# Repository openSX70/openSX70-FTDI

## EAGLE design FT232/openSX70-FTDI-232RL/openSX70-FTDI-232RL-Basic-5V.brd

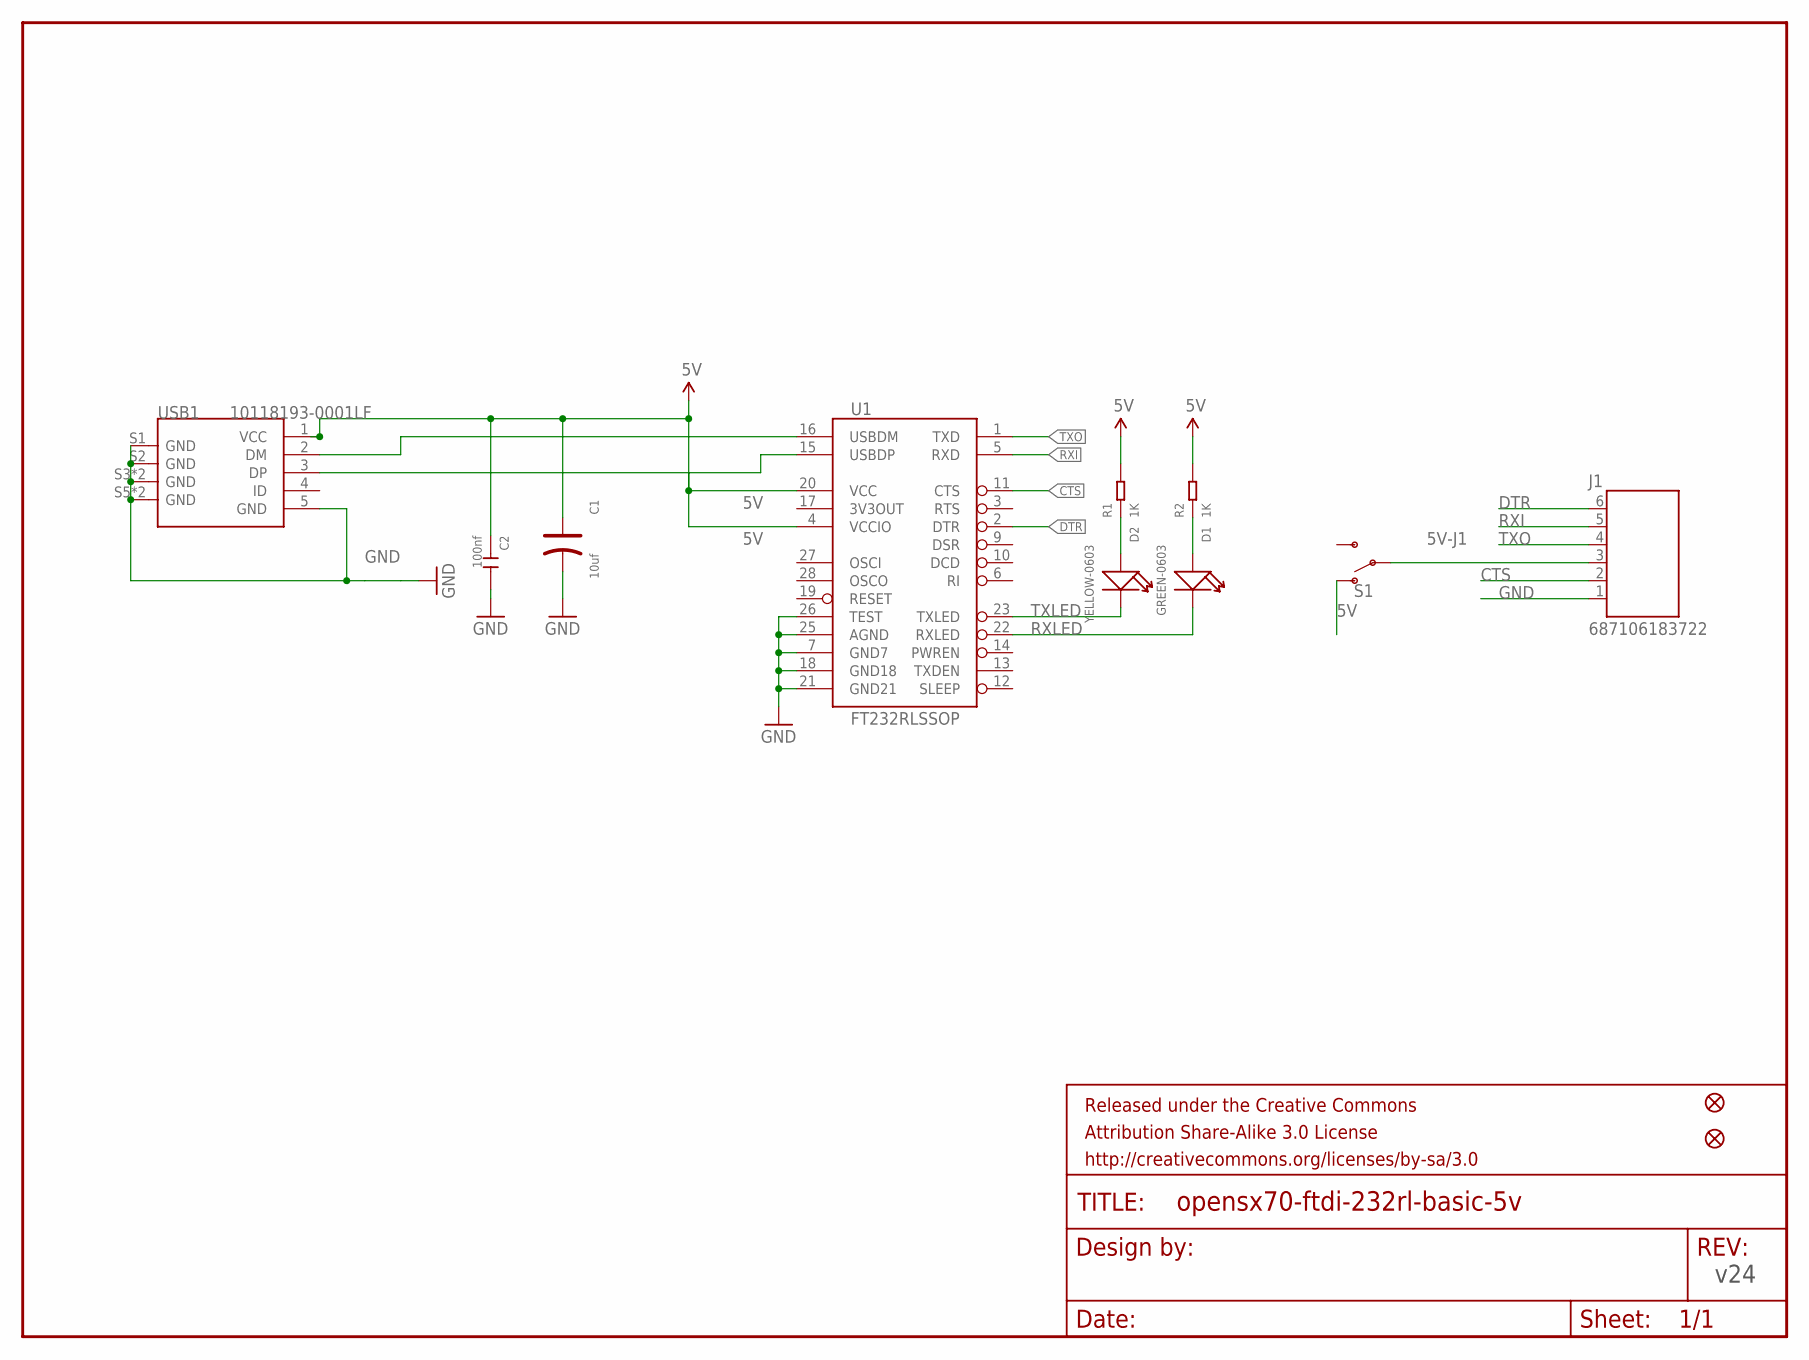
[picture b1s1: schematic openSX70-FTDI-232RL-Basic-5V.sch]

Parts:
C1: 10uf; AVX-A
C2: 100nf; C0603
D1: GREEN-0603; LED-0603
D2: YELLOW-0603; LED-0603
FRAME1: FRAME-LETTER; CREATIVE_COMMONS
J1: 687106183722
JP3, JP5: FIDUCIAL1X2; FIDUCIAL-1X2
R1, R2: 1K; R0603
S1: SWITCH-SPDT-SMD-RIGHT-ANGLE; SWITCH_SPST_SMD_A
U1: FT232RLSSOP; SSOP28DB
USB1: 10118193-0001LF; MICRO-USB5+6P-SMD-0.65-B

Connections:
5V: C1.+, C2.1, R1.2, R2.2, S1.1 (O), U1.4 (VCCIO), U1.20 (VCC), USB1.1 (VCC)
5V-J1: J1.3 (4), S1.2
CTS: J1.2 (5), U1.11 (CTS)
DTR: J1.6 (1), U1.2 (DTR)
GND: C1.-, C2.2, J1.1 (6), U1.7 (GND7), U1.18 (GND18), U1.21 (GND21), U1.25 (AGND), U1.26 (TEST), USB1.5 (GND), USB1.S1 (GND), USB1.S2 (GND), USB1.S3 (GND), USB1.S4 (GND), USB1.S5 (GND), USB1.S6 (GND)
unnamed: D2.+, R1.1
unnamed: D1.+, R2.1
unnamed: U1.16 (USBDM), USB1.2 (DM)
RXI: J1.5 (2), U1.5 (RXD)
RXLED: D1.-, U1.22 (RXLED)
TXLED: D2.-, U1.23 (TXLED)
TXO: J1.4 (3), U1.1 (TXD)
USB_D+: U1.15 (USBDP), USB1.3 (DP)

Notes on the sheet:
v24

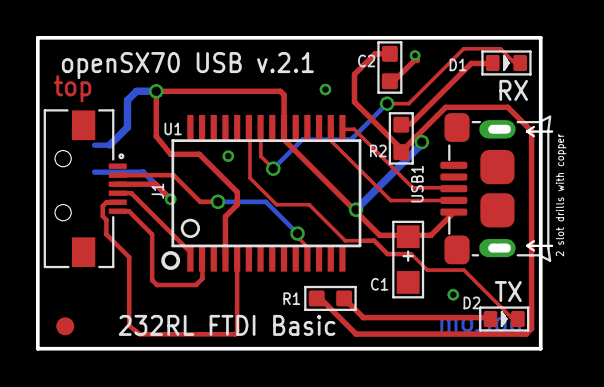
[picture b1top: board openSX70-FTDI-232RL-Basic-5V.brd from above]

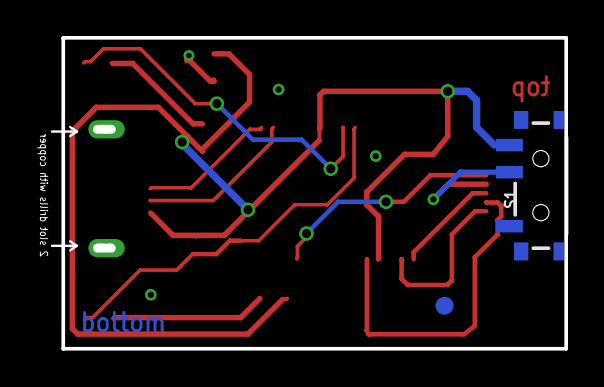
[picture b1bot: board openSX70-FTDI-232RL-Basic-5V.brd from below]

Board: 2 copper layers, 28.6 x 17.3 mm, 13 parts (2 on the bottom side), 13 nets.

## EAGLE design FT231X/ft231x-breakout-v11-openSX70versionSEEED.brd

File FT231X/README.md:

# openSX70-FTDI
FTDI connection to program openSX70 camera

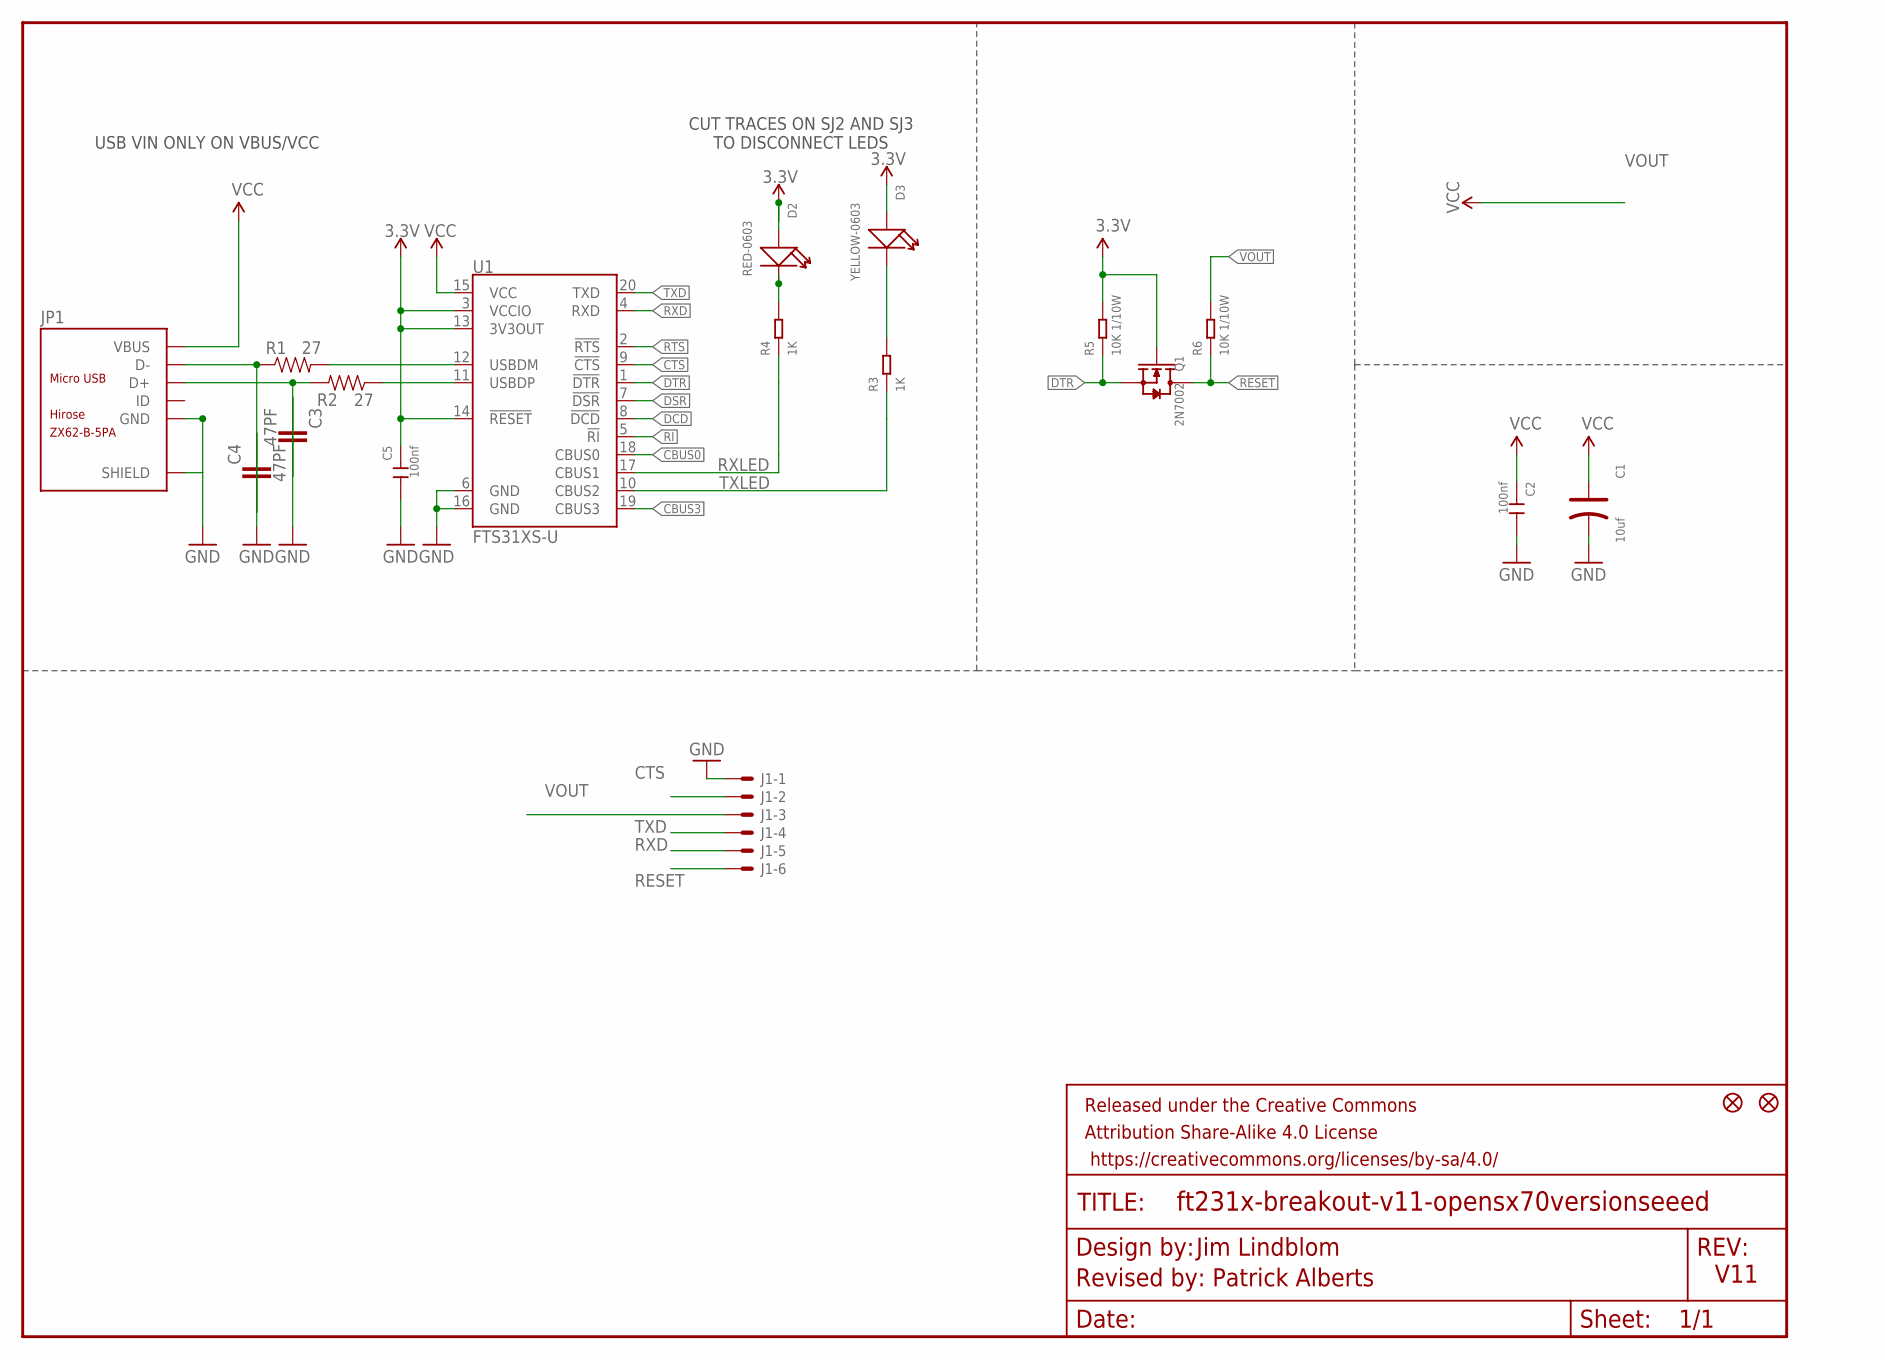
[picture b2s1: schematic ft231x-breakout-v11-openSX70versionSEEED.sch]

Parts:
C1: 10uf; AVX-B
C2, C5: 100nf; C0603
C3, C4: 47PF; CC0603KRX7R9BB473_CAPC1608X90
D2: RED-0603; LED-0603
D3: YELLOW-0603; LED-0603
FRAME1: FRAME-LETTER; CREATIVE_COMMONS
J1: XF2L-0625-1
JP1: ZX62-B-5PA; MICRO-USB5+6P-SMD-0.65-AB
JP5, JP6: FIDUCIAL1X2; FIDUCIAL-1X2
Q1: 2N7002; SOT-23
R1, R2: 27; 0603-RES
R3, R4: 1K; R0603
R5, R6: 10K 1/10W; R0603
U1: FTS31XS-U; SSOP20_L

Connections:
3.3V: C5.1, D2.+, D3.+, Q1.1 (G), R5.2, U1.3 (VCCIO), U1.13 (3V3OUT), U1.14 (!RESET)
CBUS0: U1.18 (CBUS0)
CBUS3: U1.19 (CBUS3)
CTS: J1.2, U1.9 (!CTS)
DCD: U1.8 (!DCD)
DSR: U1.7 (!DSR)
DTR: Q1.2 (S), R5.1, U1.1 (!DTR)
GND: C1.-, C2.2, C3.2, C4.2, C5.2, J1.1, JP1.5 (GND), JP1.P1 (SHIELD), JP1.P2 (SHIELD), JP1.P3_1 (SHIELD), JP1.P3_2 (SHIELD), JP1.P3_3 (SHIELD), JP1.P4_1 (SHIELD), JP1.P4_2 (SHIELD), JP1.P4_3 (SHIELD), JP1.P5 (SHIELD), JP1.P6 (SHIELD), U1.6 (GND), U1.16 (GND)
unnamed: R1.2, U1.12 (USBDM)
unnamed: R2.1, U1.11 (USBDP)
unnamed: C3.1, JP1.3 (D+), R2.2
unnamed: C4.1, JP1.2 (D-), R1.1
unnamed: D3.-, R3.2
unnamed: D2.-, R4.2
RESET: J1.6, Q1.3 (D), R6.1
RI: U1.5 (!RI)
RTS: U1.2 (!RTS)
RXD: J1.5, U1.4 (RXD)
RXLED: R4.1, U1.17 (CBUS1)
TXD: J1.4, U1.20 (TXD)
TXLED: R3.1, U1.10 (CBUS2)
VCC: C1.+, C2.1, JP1.1 (VBUS), U1.15 (VCC)
VOUT: J1.3, R6.2

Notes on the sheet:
V11
Jim Lindblom
Revised by: Patrick Alberts
USB VIN ONLY ON VBUS/VCC
CUT TRACES ON SJ2 AND SJ3 TO DISCONNECT LEDS

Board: 2 copper layers, 20 parts (0 on the bottom side), 17 nets, no tracks yet.

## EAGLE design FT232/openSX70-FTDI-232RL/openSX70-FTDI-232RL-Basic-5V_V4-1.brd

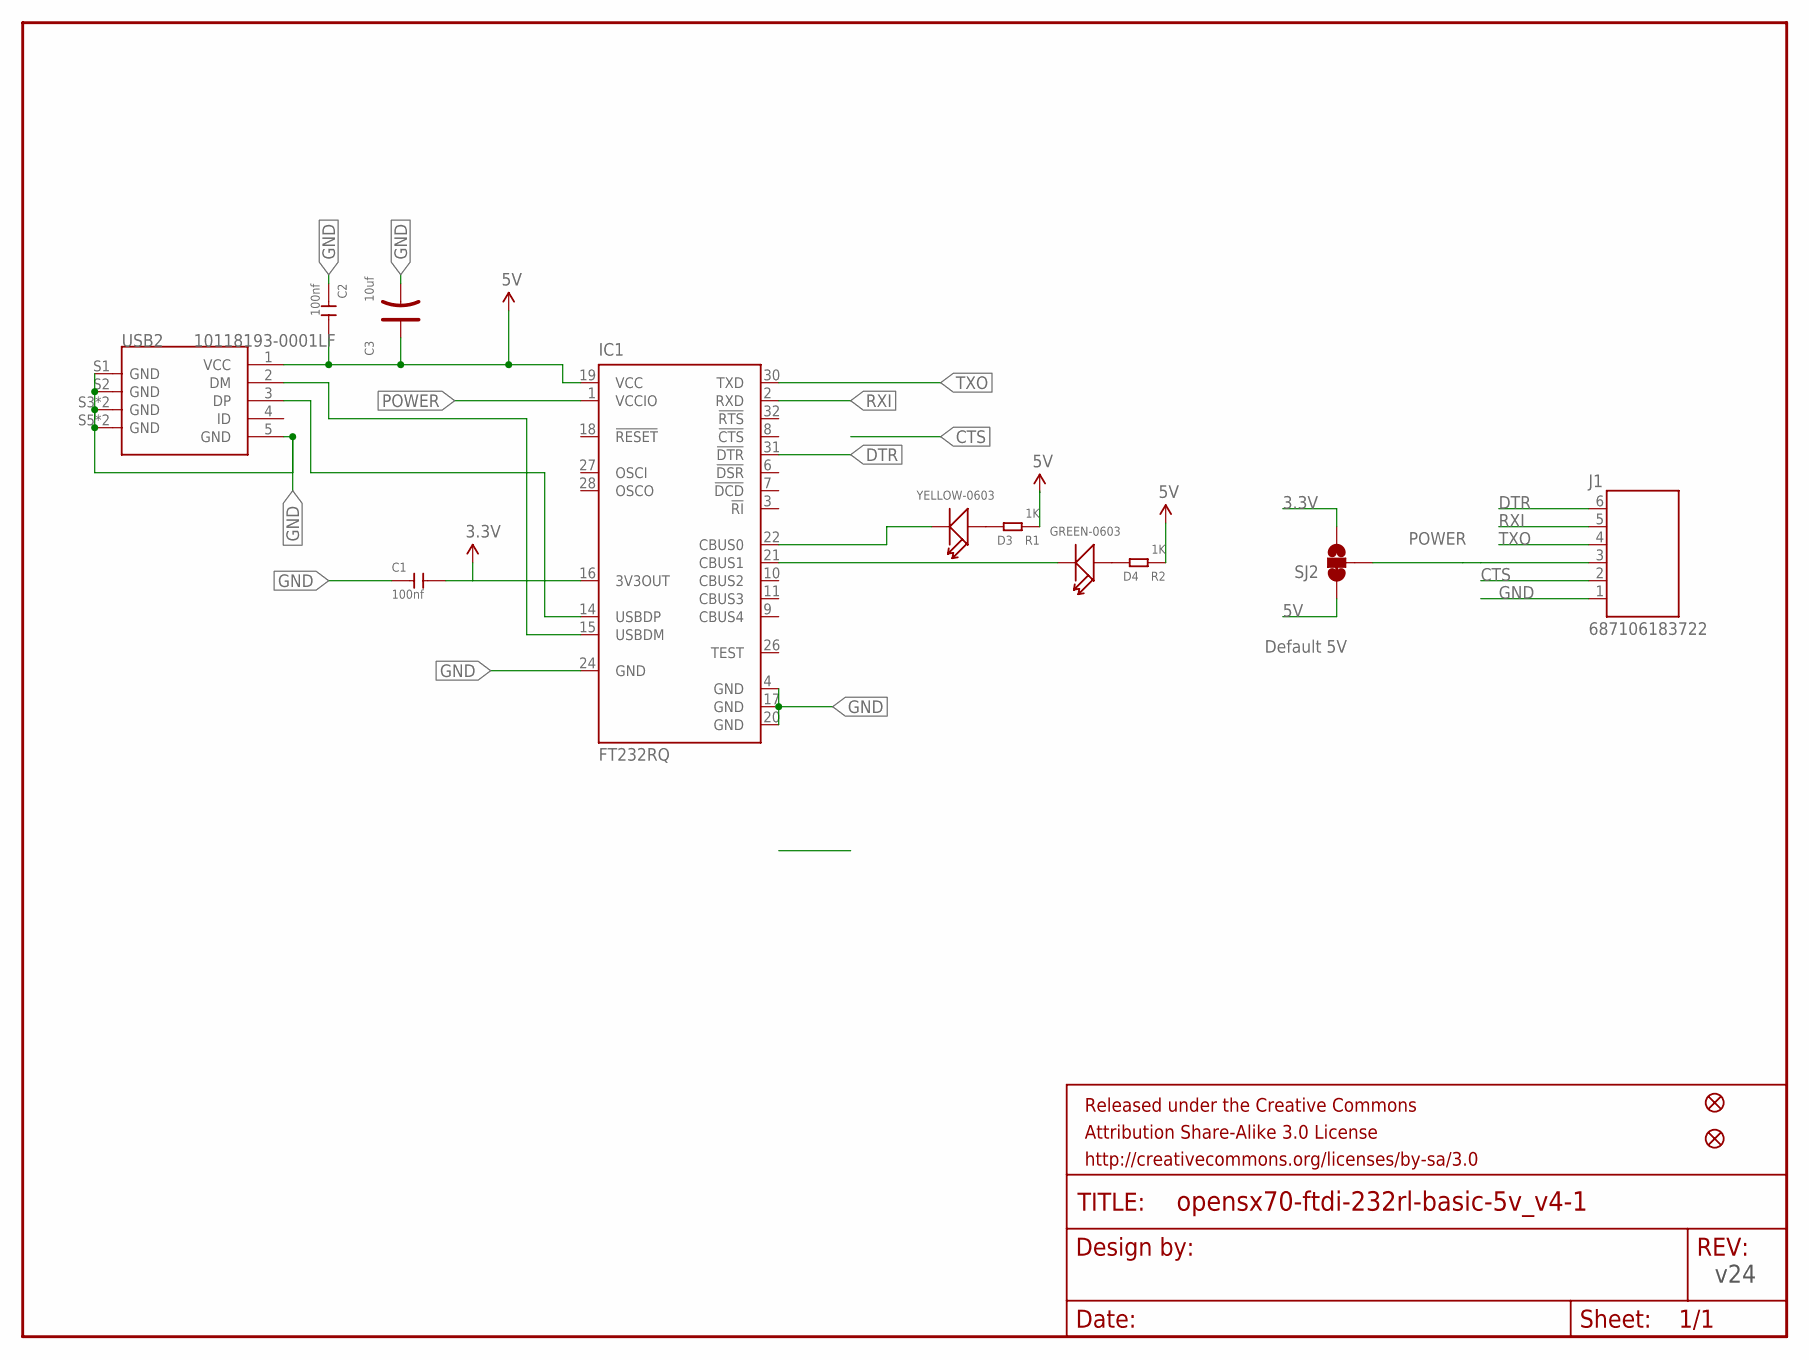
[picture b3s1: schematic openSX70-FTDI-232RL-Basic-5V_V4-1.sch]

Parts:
C1, C2: 100nf; C0603
C3: 10uf; AVX-A
D3: YELLOW-0603; LED-0603
D4: GREEN-0603; LED-0603
FRAME1: FRAME-LETTER; CREATIVE_COMMONS
IC1: FT232RQ; QFN32
J1: 687106183722
JP3, JP5: FIDUCIAL1X2; FIDUCIAL-1X2
R1, R2: 1K; R0603
SJ2: SOLDERJUMPER_2WAYS; SJ_3
USB2: 10118193-0001LF; MICRO-USB5+6P-SMD-0.65-B

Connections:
3.3V: SJ2.3
5V: C2.2, C3.+, IC1.19 (VCC), R1.1, R2.1, SJ2.1, USB2.1 (VCC)
CTS: IC1.8 (!CTS), J1.2 (5)
DTR: IC1.31 (!DTR), J1.6 (1)
GND: C1.1, C2.1, C3.-, IC1.4 (GND), IC1.17 (GND), IC1.20 (GND), IC1.24 (GND), J1.1 (6), USB2.5 (GND), USB2.S1 (GND), USB2.S2 (GND), USB2.S3 (GND), USB2.S4 (GND), USB2.S5 (GND), USB2.S6 (GND)
unnamed: IC1.15 (USBDM), USB2.2 (DM)
unnamed: IC1.14 (USBDP), USB2.3 (DP)
unnamed: D3.-, IC1.22 (CBUS0)
unnamed: D4.-, IC1.21 (CBUS1)
unnamed: D3.+, R1.2
unnamed: D4.+, R2.2
POWER: IC1.1 (VCCIO), J1.3 (4), SJ2.2
RXI: IC1.2 (RXD), J1.5 (2)
TXO: IC1.30 (TXD), J1.4 (3)
VCC: C1.2, IC1.16 (3V3OUT)

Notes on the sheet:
Default 5V
v24

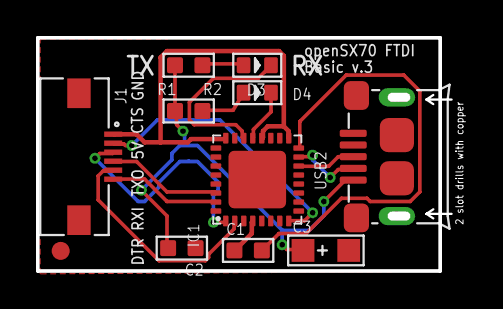
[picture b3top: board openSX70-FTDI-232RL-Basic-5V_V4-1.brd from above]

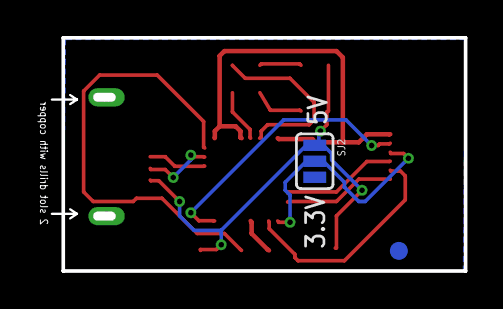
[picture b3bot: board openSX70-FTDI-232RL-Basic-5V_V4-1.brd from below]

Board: 2 copper layers, 23.0 x 13.0 mm, 14 parts (2 on the bottom side), 14 nets.

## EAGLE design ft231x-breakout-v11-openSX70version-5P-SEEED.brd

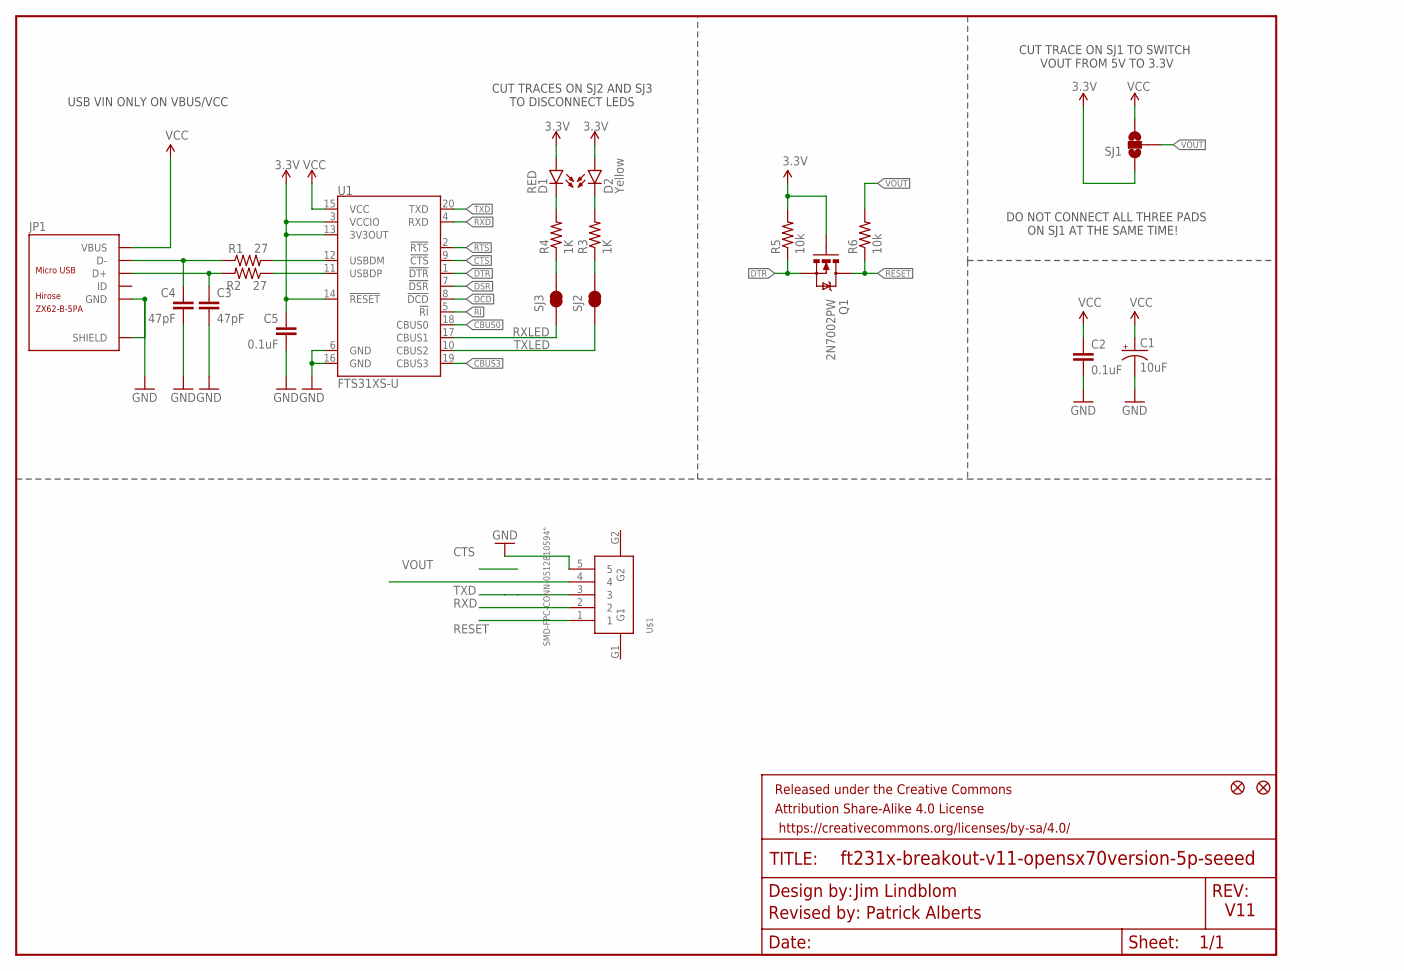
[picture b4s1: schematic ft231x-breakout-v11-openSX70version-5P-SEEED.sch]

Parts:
C1: 10uF; EIA3216
C2, C5: 0.1uF; 0603-CAP
C3, C4: 47pF; 0603-CAP
D1: RED; LED-0603
D2: Yellow; LED-0603
FRAME1: FRAME-LETTER; CREATIVE_COMMONS
JP1: ZX62-B-5PA; MICRO-USB5+6P-SMD-0.65-AB
JP5, JP6: FIDUCIAL1X2; FIDUCIAL-1X2
Q1: 2N7002PW; SOT323
R1, R2: 27; 0603-RES
R3, R4: 1K; 0603-RES
R5, R6: 10k; 0603-RES@1
SJ1: SOLDERJUMPER_2WAYS; SJ_3
SJ2: TXLED; SJ_2S-TRACE
SJ3: RXLED; PAD-JUMPER-2-NC_BY_TRACE_YES_SILK
U1: FTS31XS-U; SSOP20_L
U$1: SMD-FPC-CONN-0512810594"; 51281-0594

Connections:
3.3V: C5.1, D1.A, D2.A, Q1.1 (G), R5.2, SJ1.1, U1.3 (VCCIO), U1.13 (3V3OUT), U1.14 (!RESET)
CBUS0: U1.18 (CBUS0)
CBUS3: U1.19 (CBUS3)
CTS: U1.9 (!CTS)
DCD: U1.8 (!DCD)
DSR: U1.7 (!DSR)
DTR: Q1.2 (S), R5.1, U1.1 (!DTR)
GND: C1.C (-), C2.2, C3.2, C4.2, C5.2, JP1.5 (GND), JP1.P1 (SHIELD), JP1.P2 (SHIELD), JP1.P3 (SHIELD), JP1.P4 (SHIELD), JP1.P5 (SHIELD), JP1.P6 (SHIELD), U1.6 (GND), U1.16 (GND), U$1.5
unnamed: R1.2, U1.12 (USBDM)
unnamed: R2.1, U1.11 (USBDP)
unnamed: C3.1, JP1.3 (D+), R2.2
unnamed: C4.1, JP1.2 (D-), R1.1
unnamed: D2.C, R3.2
unnamed: D1.C, R4.2
unnamed: R3.1, SJ2.2
unnamed: R4.1, SJ3.2
RESET: Q1.3 (D), R6.1, U$1.1
RI: U1.5 (!RI)
RTS: U1.2 (!RTS)
RXD: U1.4 (RXD), U$1.2
RXLED: SJ3.1, U1.17 (CBUS1)
TXD: U1.20 (TXD), U$1.3
TXLED: SJ2.1, U1.10 (CBUS2)
VCC: C1.A (+), C2.1, JP1.1 (VBUS), SJ1.3, U1.15 (VCC)
VOUT: R6.2, SJ1.2, U$1.4

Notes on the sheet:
V11
Jim Lindblom
Revised by: Patrick Alberts
USB VIN ONLY ON VBUS/VCC
CUT TRACES ON SJ2 AND SJ3 TO DISCONNECT LEDS
CUT TRACE ON SJ1 TO SWITCH VOUT FROM 5V TO 3.3V
DO NOT CONNECT ALL THREE PADS ON SJ1 AT THE SAME TIME!

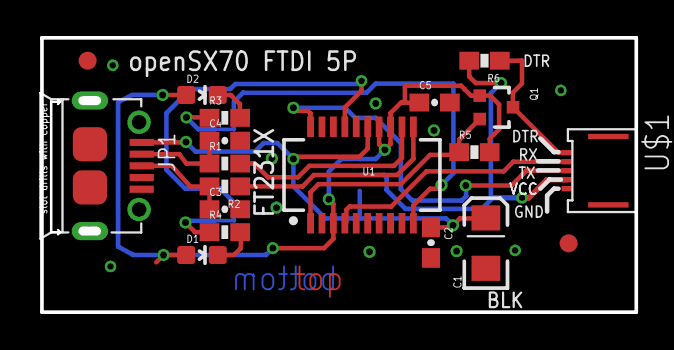
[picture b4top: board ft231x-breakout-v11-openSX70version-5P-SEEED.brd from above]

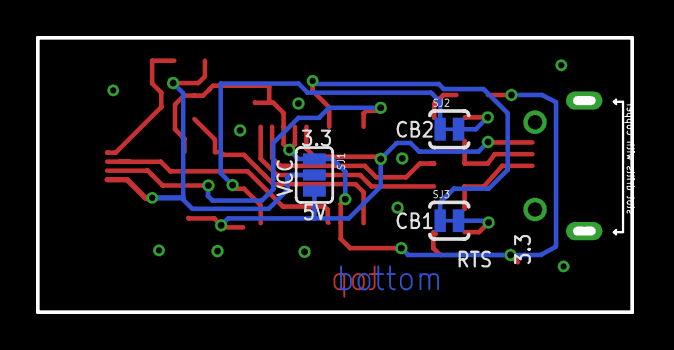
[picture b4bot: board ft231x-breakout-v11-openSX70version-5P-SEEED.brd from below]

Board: 2 copper layers, 33.0 x 15.2 mm, 23 parts (3 on the bottom side), 18 nets.

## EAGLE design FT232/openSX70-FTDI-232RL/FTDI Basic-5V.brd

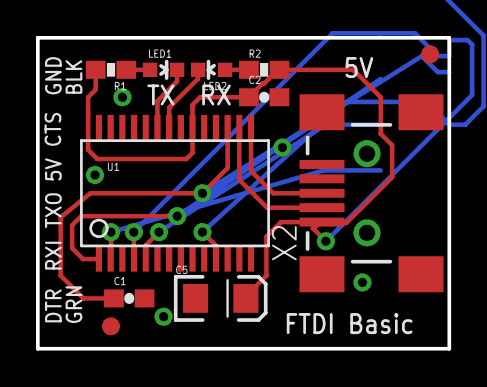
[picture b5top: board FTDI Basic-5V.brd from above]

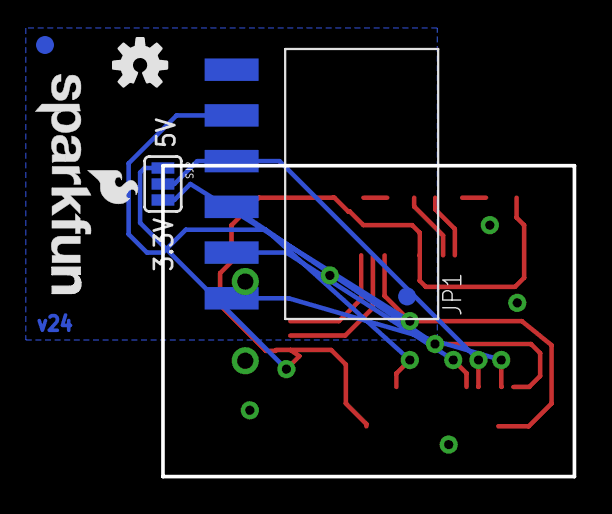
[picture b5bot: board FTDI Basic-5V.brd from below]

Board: 2 copper layers, 22.9 x 17.3 mm, 19 parts (7 on the bottom side), 14 nets.

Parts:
C1, C2: 0.1uF; 0603-CAP
C5: 10uF; EIA3216
FRAME1: FRAME-LETTER; CREATIVE_COMMONS
JP1: 1X06-SMD-FEMALE-V2
JP2: LOGO-SFESK; SFE-LOGO-FLAME
JP3, JP4, JP5, JP6: FIDUCIAL1X2; FIDUCIAL-1X2
LED1: Red; LED-0603
LED2: Green; LED-0603
LOGO1: OSHW-LOGOS; OSHW-LOGO-S
R1, R2: 1K; 0603-RES
SJ2: SJ_3
U1: FT232RLSSOP; SSOP28DB
U$2: LOGO-SFENW2; SFE-NEW-WEB
X2: USB-SMD-NS; USB-MINIB-NOSTOP

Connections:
3.3V: C1.1, SJ2.3, U1.17
5V: C2.1, C5.A, R1.2, R2.2, SJ2.1, U1.20, X2.VBUS
CTS: JP1.2, U1.11
DTR: JP1.6, U1.2
GND: C1.2, C2.2, C5.C, JP1.1, U1.7, U1.18, U1.21, U1.25, U1.26, X2.GND
unnamed: LED1.A, R1.1
unnamed: LED2.A, R2.1
POWER: JP1.3, SJ2.2, U1.4
RXI: JP1.5, U1.5
RXLED: LED2.C, U1.22
TXLED: LED1.C, U1.23
TXO: JP1.4, U1.1
USB_D+: U1.15, X2.D+
USB_D-: U1.16, X2.D-

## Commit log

2018-01-25 Initial commit to Github
2018-02-25 New 5P seeed version
2018-04-25 Seeed WIP
2018-05-08 Manufacturable FTDI
2018-05-23 New Breakout WIP
2018-05-31 SeeedStudio manufacturable
2018-05-31 Folder reorganize
2018-06-05 New FTDI versions with FT232R L and Q
2018-07-23 NEW FTDI for manufacture 232RL based on Sparkfun FTDI basic
2018-07-24 232RL + BOM WIP
2018-07-24 Fixes to power.
2018-07-24 Upgrade to 9.1.1 and fixes
2018-07-24 new FTDI FT232RL for manufacturing
2018-12-17 CSV BOM
2019-07-09 PCBWAY

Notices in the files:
parts and their libraries:
SparkFun-Aesthetics: Licensing: CC v3.0 Share-Alike You are welcome to use this library for commercial purposes.
SparkFun-Aesthetics: Released under the Creative Commons Attribution Share-Alike 4.0 License
SparkFun-Aesthetics: https://creativecommons.org/licenses/by-sa/4.0
